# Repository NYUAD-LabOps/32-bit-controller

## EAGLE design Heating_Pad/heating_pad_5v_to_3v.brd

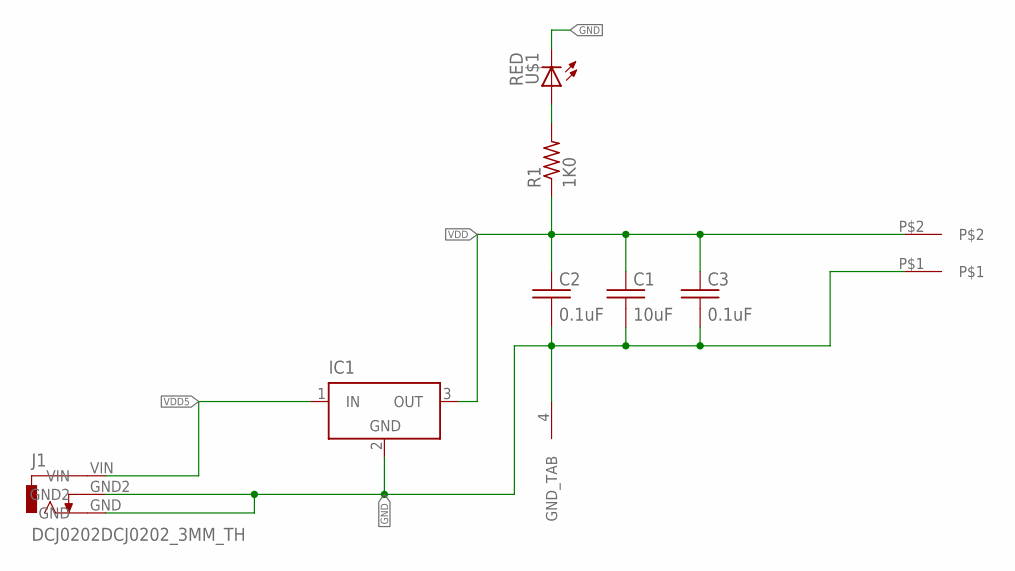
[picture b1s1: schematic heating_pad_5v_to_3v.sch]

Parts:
C1: 10uF; 0402
C2, C3: 0.1uF; 0402
IC1: LT1129CST3; SOT223
J1: DCJ0202DCJ0202_3MM_TH; DCJ0202_3MM_TH
J2: 2-pos; 2_3.81MM_PITCH
R1: 1K0; 0402
U$1: LED_0805_RED

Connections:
GND: C1.P$2 (2), C2.P$2 (2), C3.P$2 (2), IC1.2 (GND), IC1.4 (GND_TAB), J1.GND, J1.GND2, J2.P$1, U$1.C
unnamed: R1.P$2 (2), U$1.A
VDD: C1.P$1 (1), C2.P$1 (1), C3.P$1 (1), IC1.3 (OUT), J2.P$2, R1.P$1 (1)
VDD5: IC1.1 (IN), J1.VIN

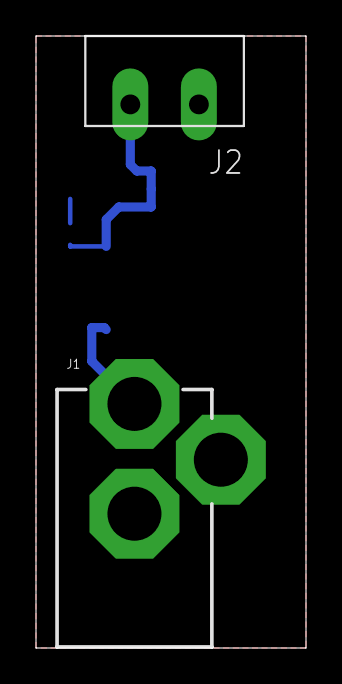
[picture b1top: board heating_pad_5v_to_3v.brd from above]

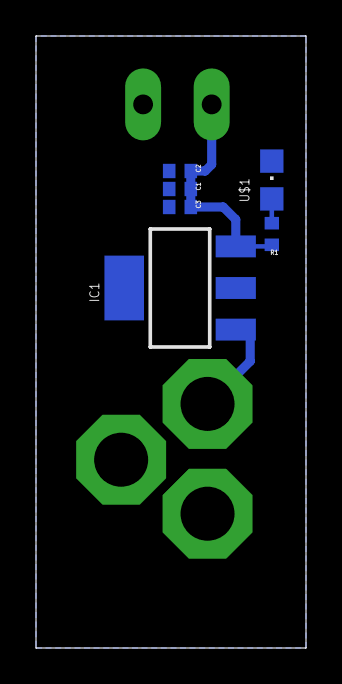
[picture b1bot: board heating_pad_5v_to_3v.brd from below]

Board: 2 copper layers, 15.0 x 34.0 mm, 8 parts (6 on the bottom side), 4 nets.

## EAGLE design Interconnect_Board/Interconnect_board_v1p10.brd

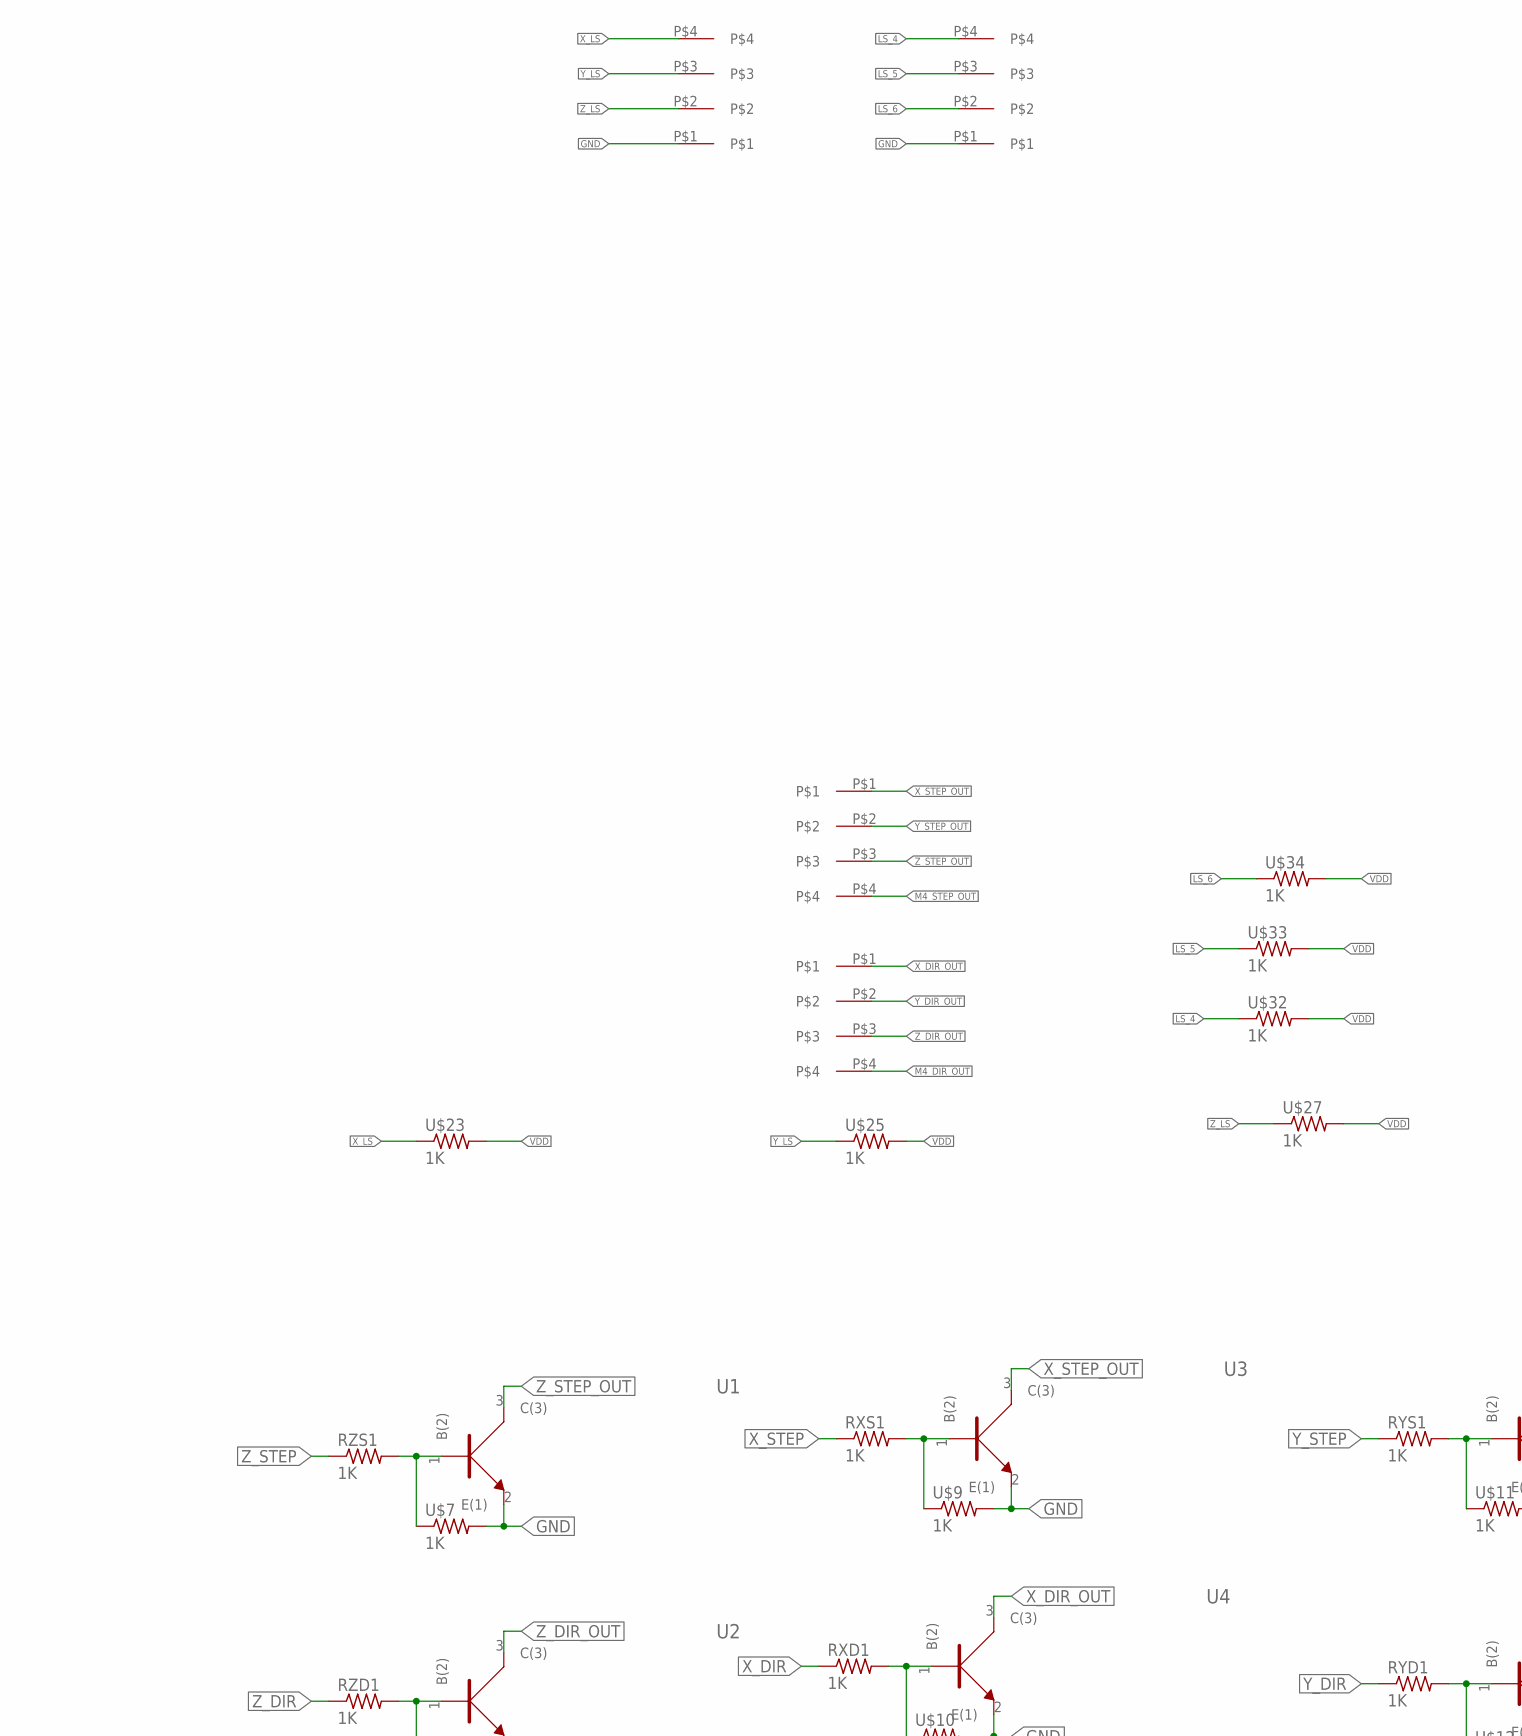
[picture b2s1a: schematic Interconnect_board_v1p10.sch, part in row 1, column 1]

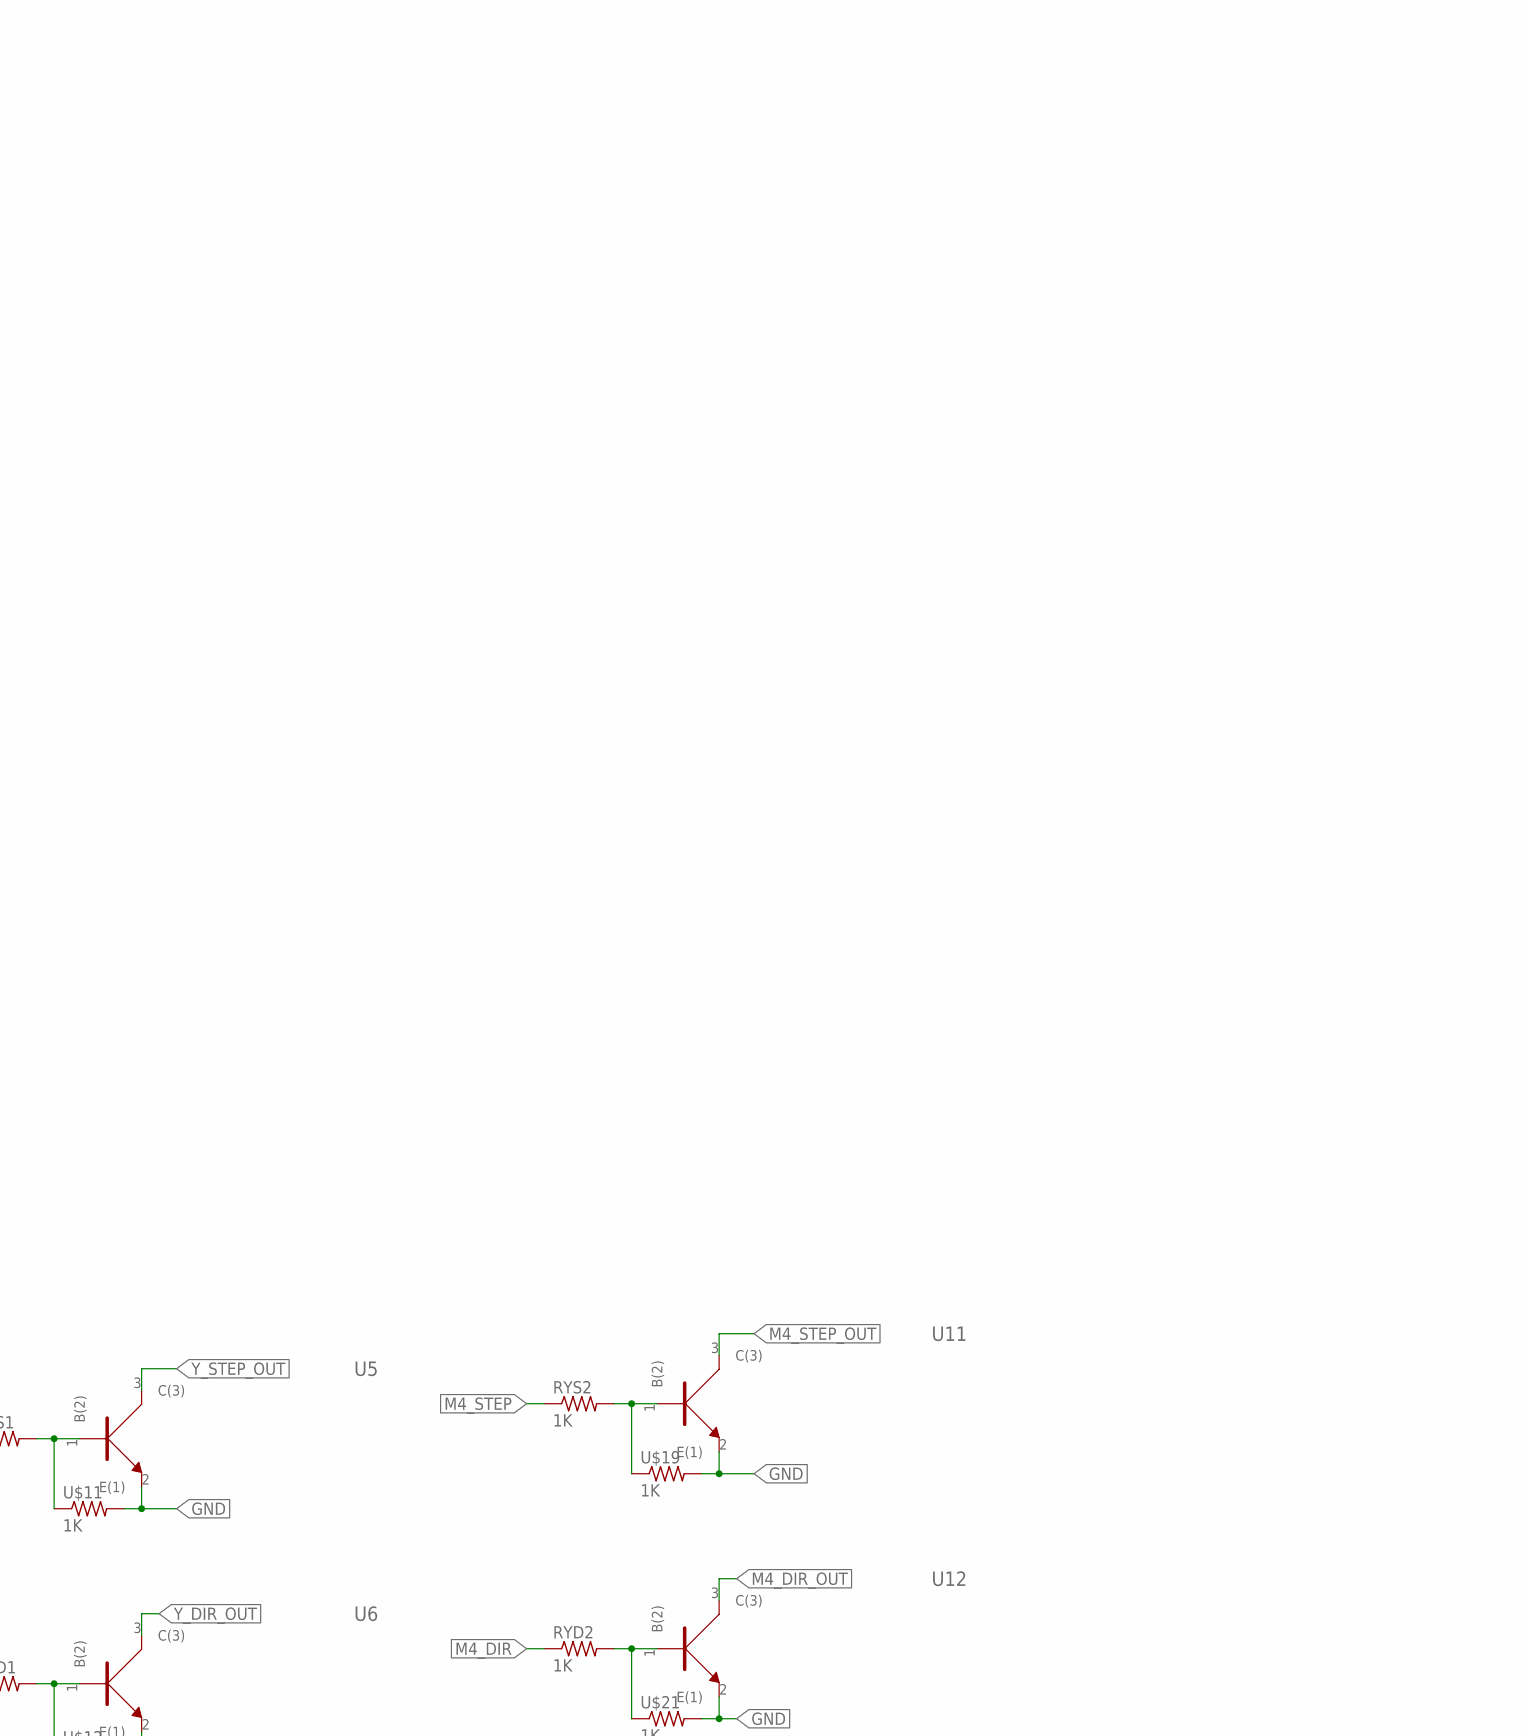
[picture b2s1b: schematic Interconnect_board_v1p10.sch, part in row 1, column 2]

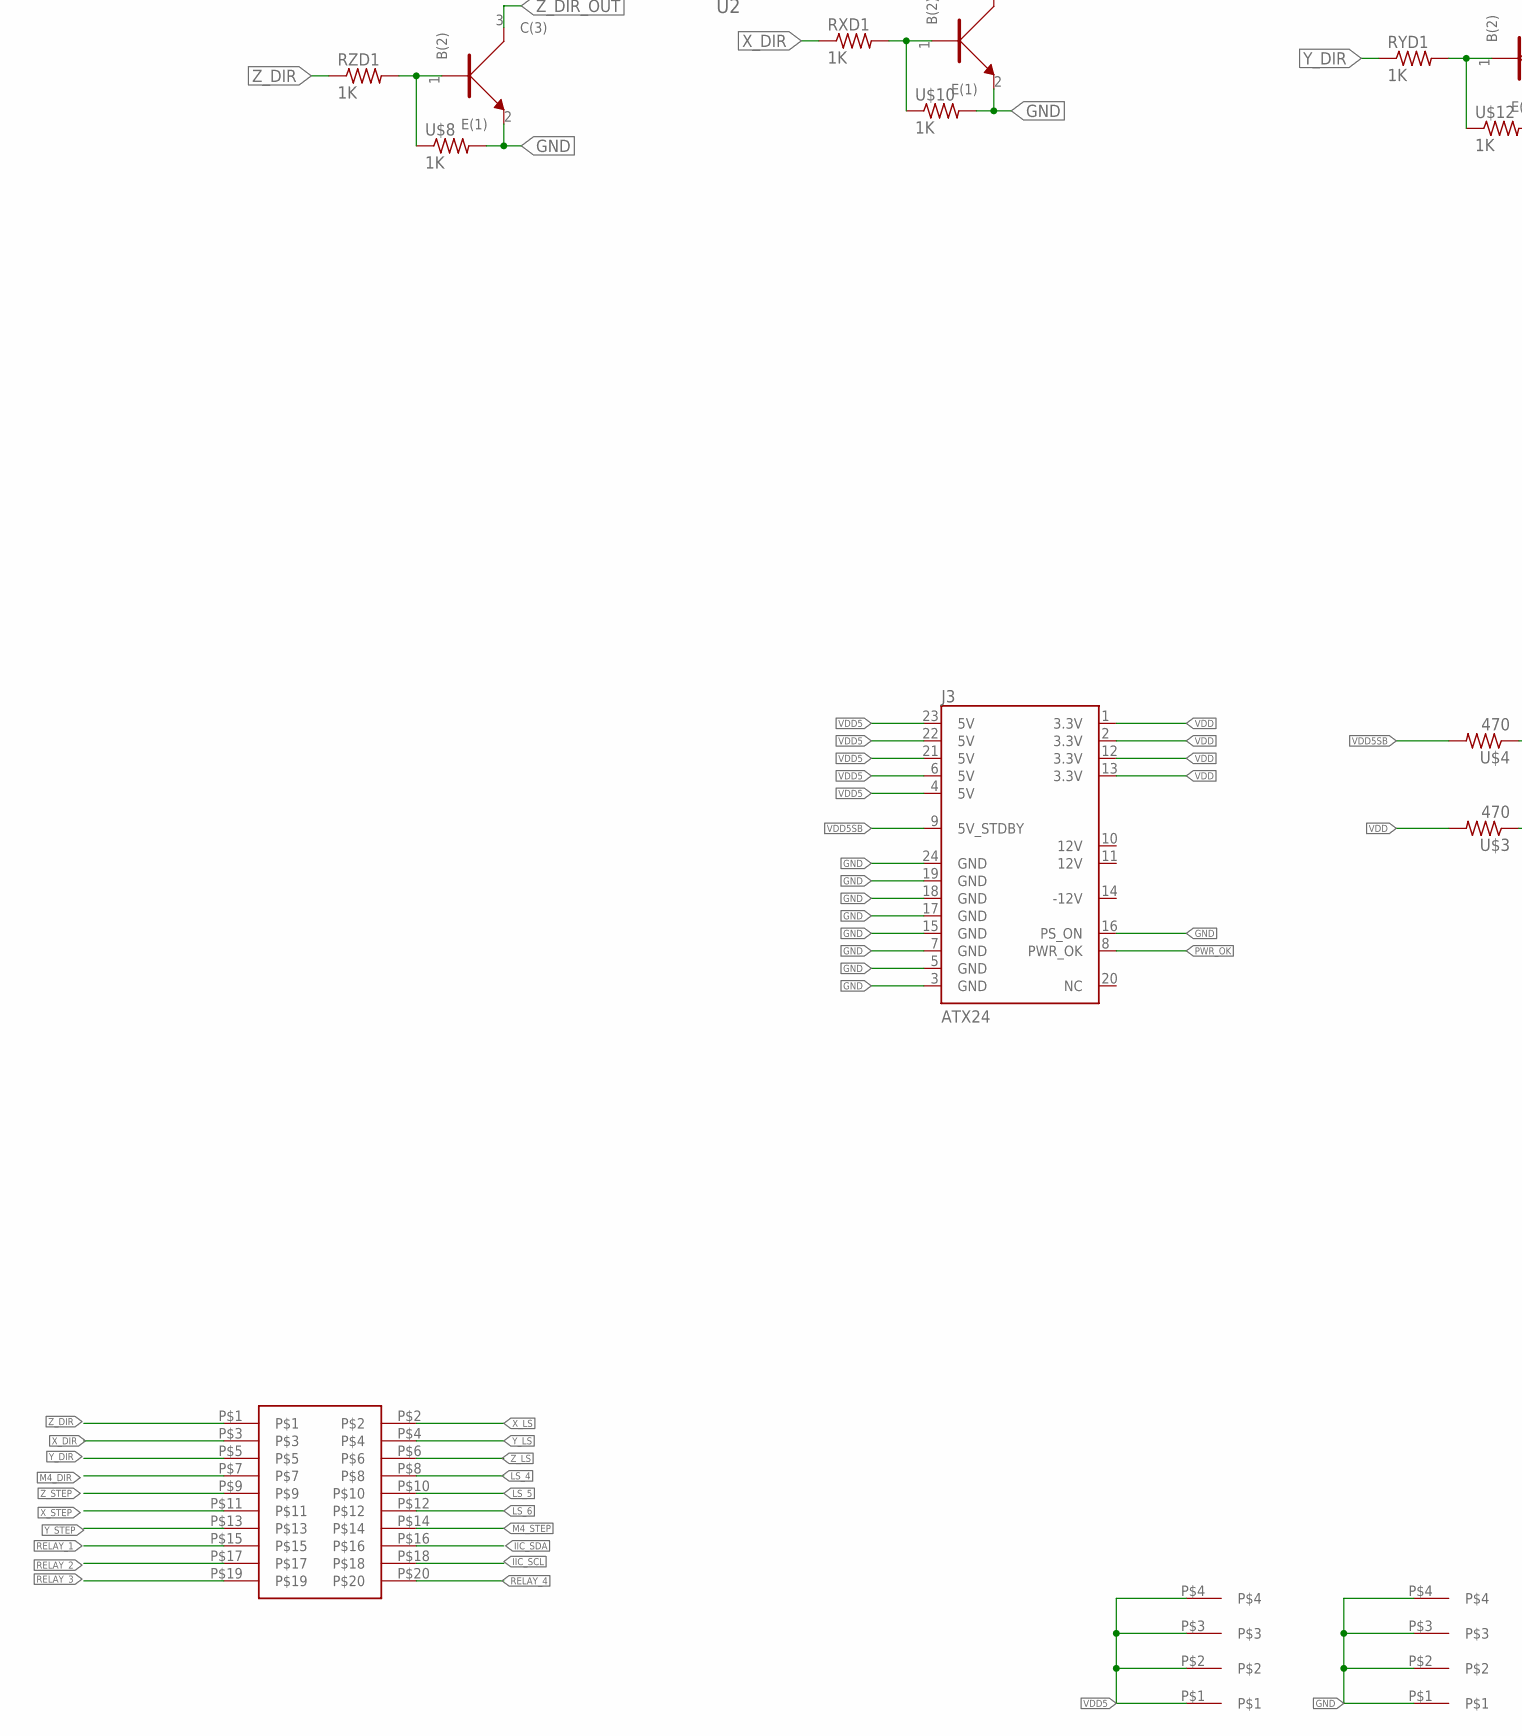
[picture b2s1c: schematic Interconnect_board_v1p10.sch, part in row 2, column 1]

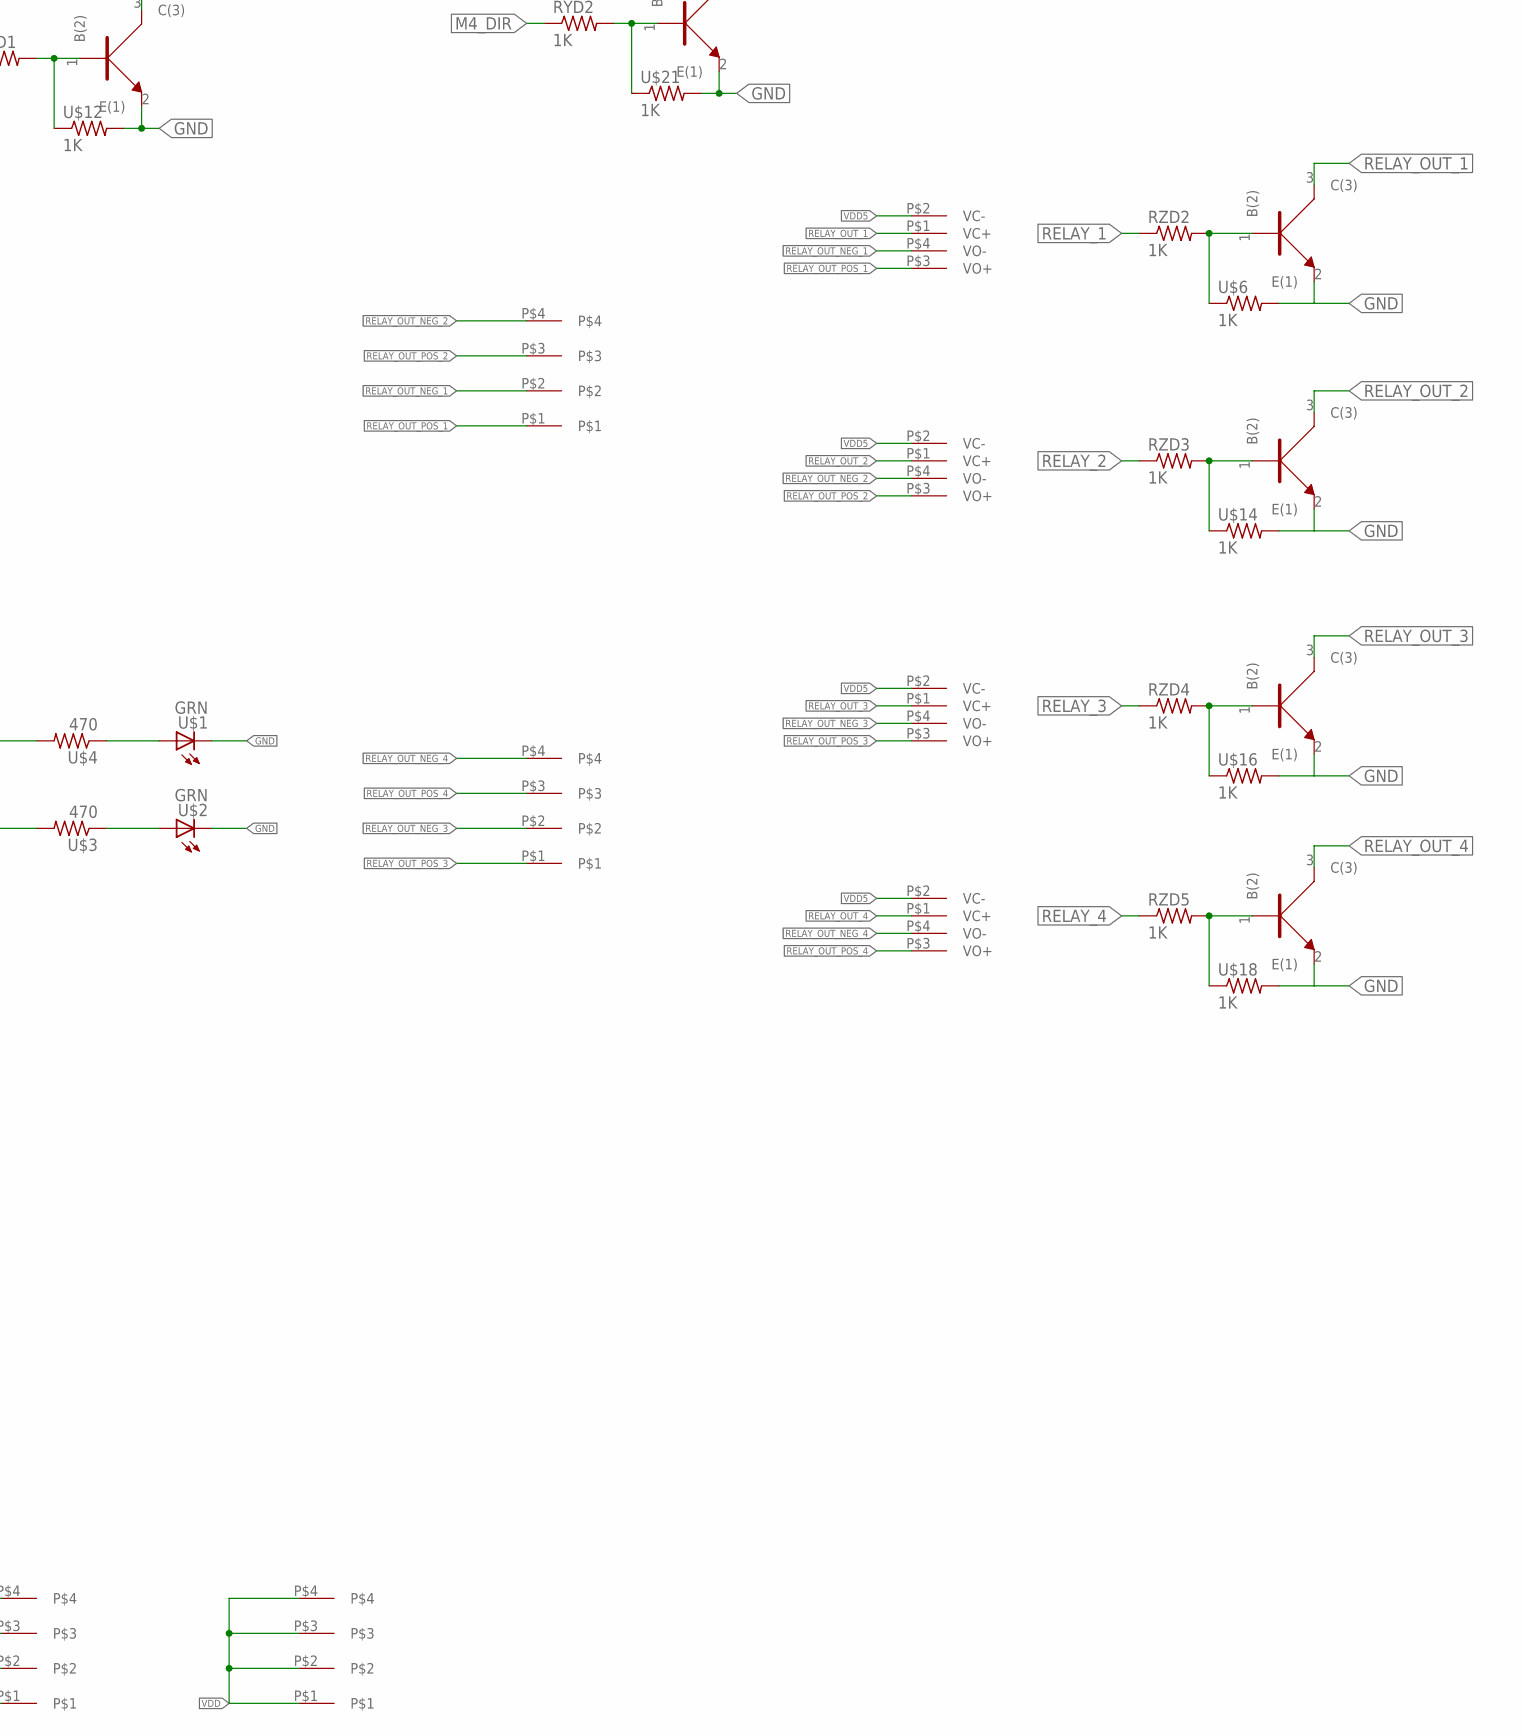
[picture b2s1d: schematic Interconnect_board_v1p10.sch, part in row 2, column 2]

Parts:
J1, J2, J4, J6, J7, J8, J9, J10, J11: 3.81MM_1_X_4_RT_ANGLE_PLUG_HEADER; 1X4_3.81MM_PITCH
J3: ATX24; ATX24_STRAIGHT
RXD1: R_0805_1K
RXS1: R_0805_1K
RYD1, RYD2: R_0805_1K
RYS1, RYS2: R_0805_1K
RZD1, RZD2, RZD3, RZD4, RZD5: R_0805_1K
RZS1: R_0805_1K
U1, U2, U3, U4, U5, U6, U7, U8, U9, U10, U11, U12: BC846BW; SOT323
U$1, U$2: LED_0805_GREEN
U$3, U$4: R_0805_470
U$5, U$13, U$15, U$17: RELAY_KYOTO_KF0604D
U$6, U$7, U$8, U$9, U$10, U$11, U$12, U$14, U$16, U$18, U$19, U$21, U$23, U$25, U$27, U$32, U$33, U$34: R_0805_1K
U$26: 2_X_10_HEADER_GENERIC; 2_X_10_.1_INCH

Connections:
GND: J1.P$1, J1.P$2, J1.P$3, J1.P$4, J3.3 (GND), J3.5 (GND), J3.7 (GND), J3.15 (GND), J3.16 (PS_ON), J3.17 (GND), J3.18 (GND), J3.19 (GND), J3.24 (GND), J10.P$1, J11.P$1, U1.2 (E(1)), U2.2 (E(1)), U3.2 (E(1)), U4.2 (E(1)), U5.2 (E(1)), U6.2 (E(1)), U7.2 (E(1)), U8.2 (E(1)), U9.2 (E(1)), U10.2 (E(1)), U11.2 (E(1)), U12.2 (E(1)), U$1.C, U$2.C, U$6.2, U$7.2, U$8.2, U$9.2, U$10.2, U$11.2, U$12.2, U$14.2, U$16.2, U$18.2, U$19.2, U$21.2
IIC_SCL: U$26.P$18
IIC_SDA: U$26.P$16
LS_4: J11.P$4, U$26.P$8, U$32.1
LS_5: J11.P$3, U$26.P$10, U$33.1
LS_6: J11.P$2, U$26.P$12, U$34.1
M4_DIR: RYD2.1, U$26.P$7
M4_DIR_OUT: J9.P$4, U12.3 (C(3))
M4_STEP: RYS2.1, U$26.P$14
M4_STEP_OUT: J8.P$4, U11.3 (C(3))
unnamed: RXS1.2, U3.1 (B(2)), U$9.1
unnamed: RZD3.2, U8.1 (B(2)), U$14.1
unnamed: RZD1.2, U2.1 (B(2)), U$8.1
unnamed: U$1.A, U$4.1
unnamed: U$2.A, U$3.1
unnamed: RZD4.2, U9.1 (B(2)), U$16.1
unnamed: RZS1.2, U1.1 (B(2)), U$7.1
unnamed: RZD2.2, U7.1 (B(2)), U$6.1
unnamed: RYS1.2, U5.1 (B(2)), U$11.1
unnamed: RZD5.2, U10.1 (B(2)), U$18.1
unnamed: RXD1.2, U4.1 (B(2)), U$10.1
unnamed: RYD1.2, U6.1 (B(2)), U$12.1
unnamed: RYS2.2, U11.1 (B(2)), U$19.1
unnamed: RYD2.2, U12.1 (B(2)), U$21.1
PWR_OK: J3.8 (PWR_OK)
RELAY_1: RZD2.1, U$26.P$15
RELAY_2: RZD3.1, U$26.P$17
RELAY_3: RZD4.1, U$26.P$19
RELAY_4: RZD5.1, U$26.P$20
RELAY_OUT_1: U7.3 (C(3)), U$5.P$1 (VC+)
RELAY_OUT_2: U8.3 (C(3)), U$13.P$1 (VC+)
RELAY_OUT_3: U9.3 (C(3)), U$15.P$1 (VC+)
RELAY_OUT_4: U10.3 (C(3)), U$17.P$1 (VC+)
RELAY_OUT_NEG_1: J6.P$2, U$5.P$4 (VO-)
RELAY_OUT_NEG_2: J6.P$4, U$13.P$4 (VO-)
RELAY_OUT_NEG_3: J7.P$2, U$15.P$4 (VO-)
RELAY_OUT_NEG_4: J7.P$4, U$17.P$4 (VO-)
RELAY_OUT_POS_1: J6.P$1, U$5.P$3 (VO+)
RELAY_OUT_POS_2: J6.P$3, U$13.P$3 (VO+)
RELAY_OUT_POS_3: J7.P$1, U$15.P$3 (VO+)
RELAY_OUT_POS_4: J7.P$3, U$17.P$3 (VO+)
VDD: J2.P$1, J2.P$2, J2.P$3, J2.P$4, J3.1 (3.3V), J3.2 (3.3V), J3.12 (3.3V), J3.13 (3.3V), U$3.2, U$23.2, U$25.2, U$27.2, U$32.2, U$33.2, U$34.2
VDD5: J3.4 (5V), J3.6 (5V), J3.21 (5V), J3.22 (5V), J3.23 (5V), J4.P$1, J4.P$2, J4.P$3, J4.P$4, U$5.P$2 (VC-), U$13.P$2 (VC-), U$15.P$2 (VC-), U$17.P$2 (VC-)
VDD5SB: J3.9 (5V_STDBY), U$4.2
X_DIR: RXD1.1, U$26.P$3
X_DIR_OUT: J9.P$1, U4.3 (C(3))
X_LS: J10.P$4, U$23.1, U$26.P$2
X_STEP: RXS1.1, U$26.P$11
X_STEP_OUT: J8.P$1, U3.3 (C(3))
Y_DIR: RYD1.1, U$26.P$5
Y_DIR_OUT: J9.P$2, U6.3 (C(3))
Y_LS: J10.P$3, U$25.1, U$26.P$4
Y_STEP: RYS1.1, U$26.P$13
Y_STEP_OUT: J8.P$2, U5.3 (C(3))
Z_DIR: RZD1.1, U$26.P$1
Z_DIR_OUT: J9.P$3, U2.3 (C(3))
Z_LS: J10.P$2, U$26.P$6, U$27.1
Z_STEP: RZS1.1, U$26.P$9
Z_STEP_OUT: J8.P$3, U1.3 (C(3))

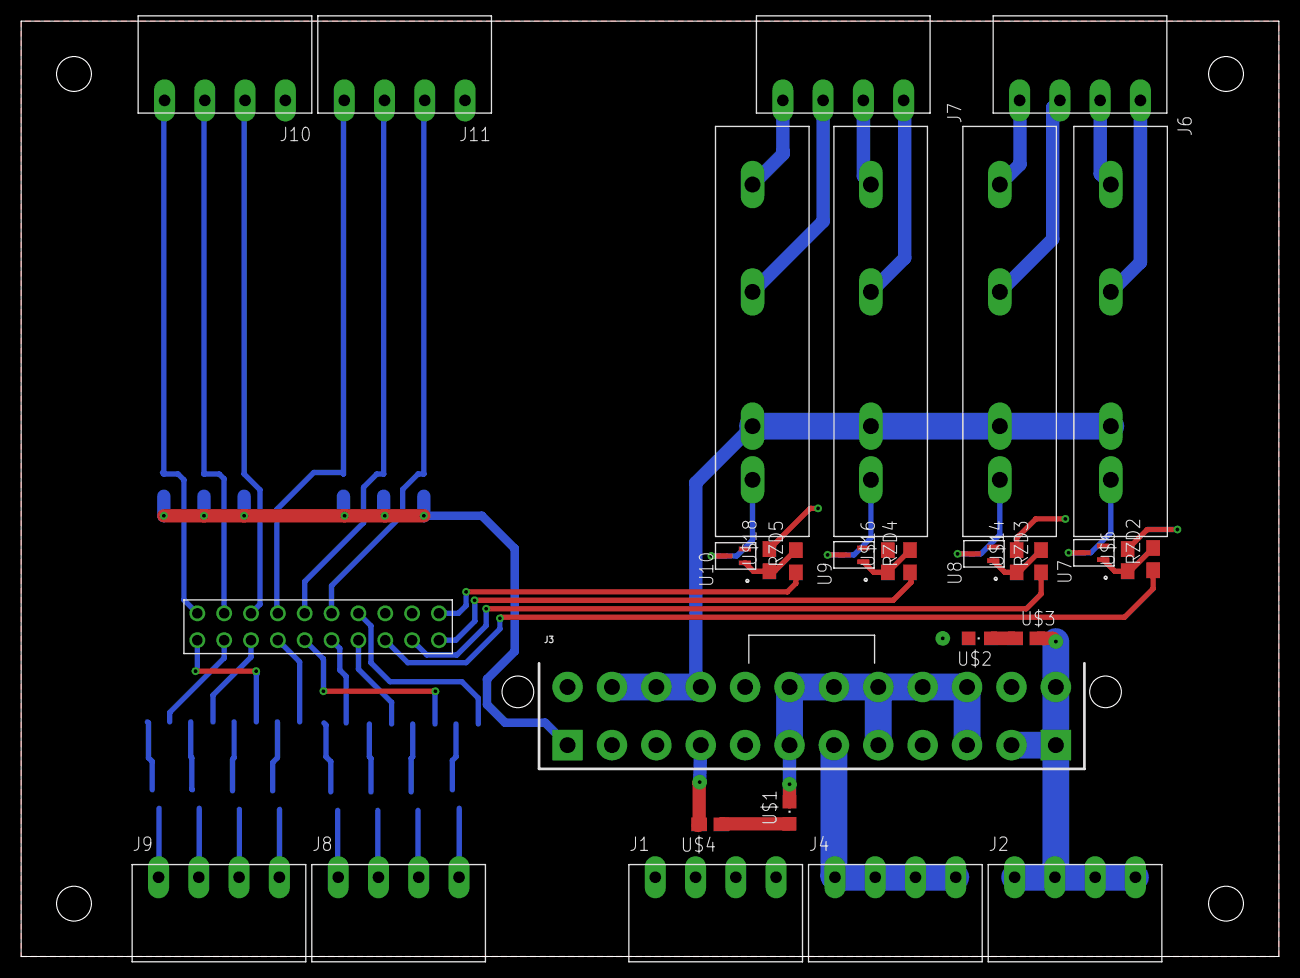
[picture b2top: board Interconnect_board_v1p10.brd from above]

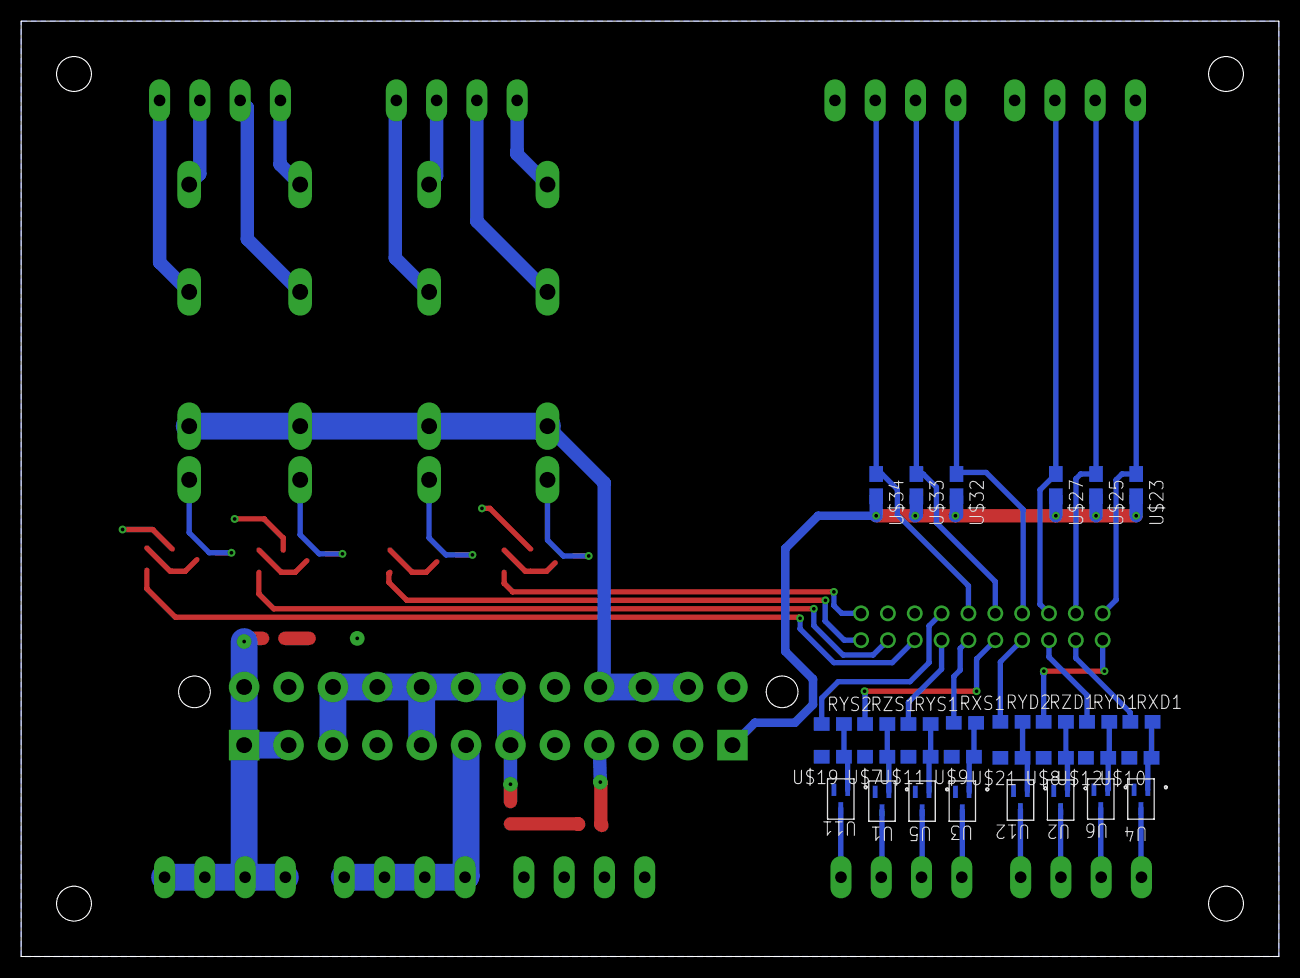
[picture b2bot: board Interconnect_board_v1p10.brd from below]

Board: 2 copper layers, 119.0 x 88.5 mm, 61 parts (30 on the bottom side), 56 nets.

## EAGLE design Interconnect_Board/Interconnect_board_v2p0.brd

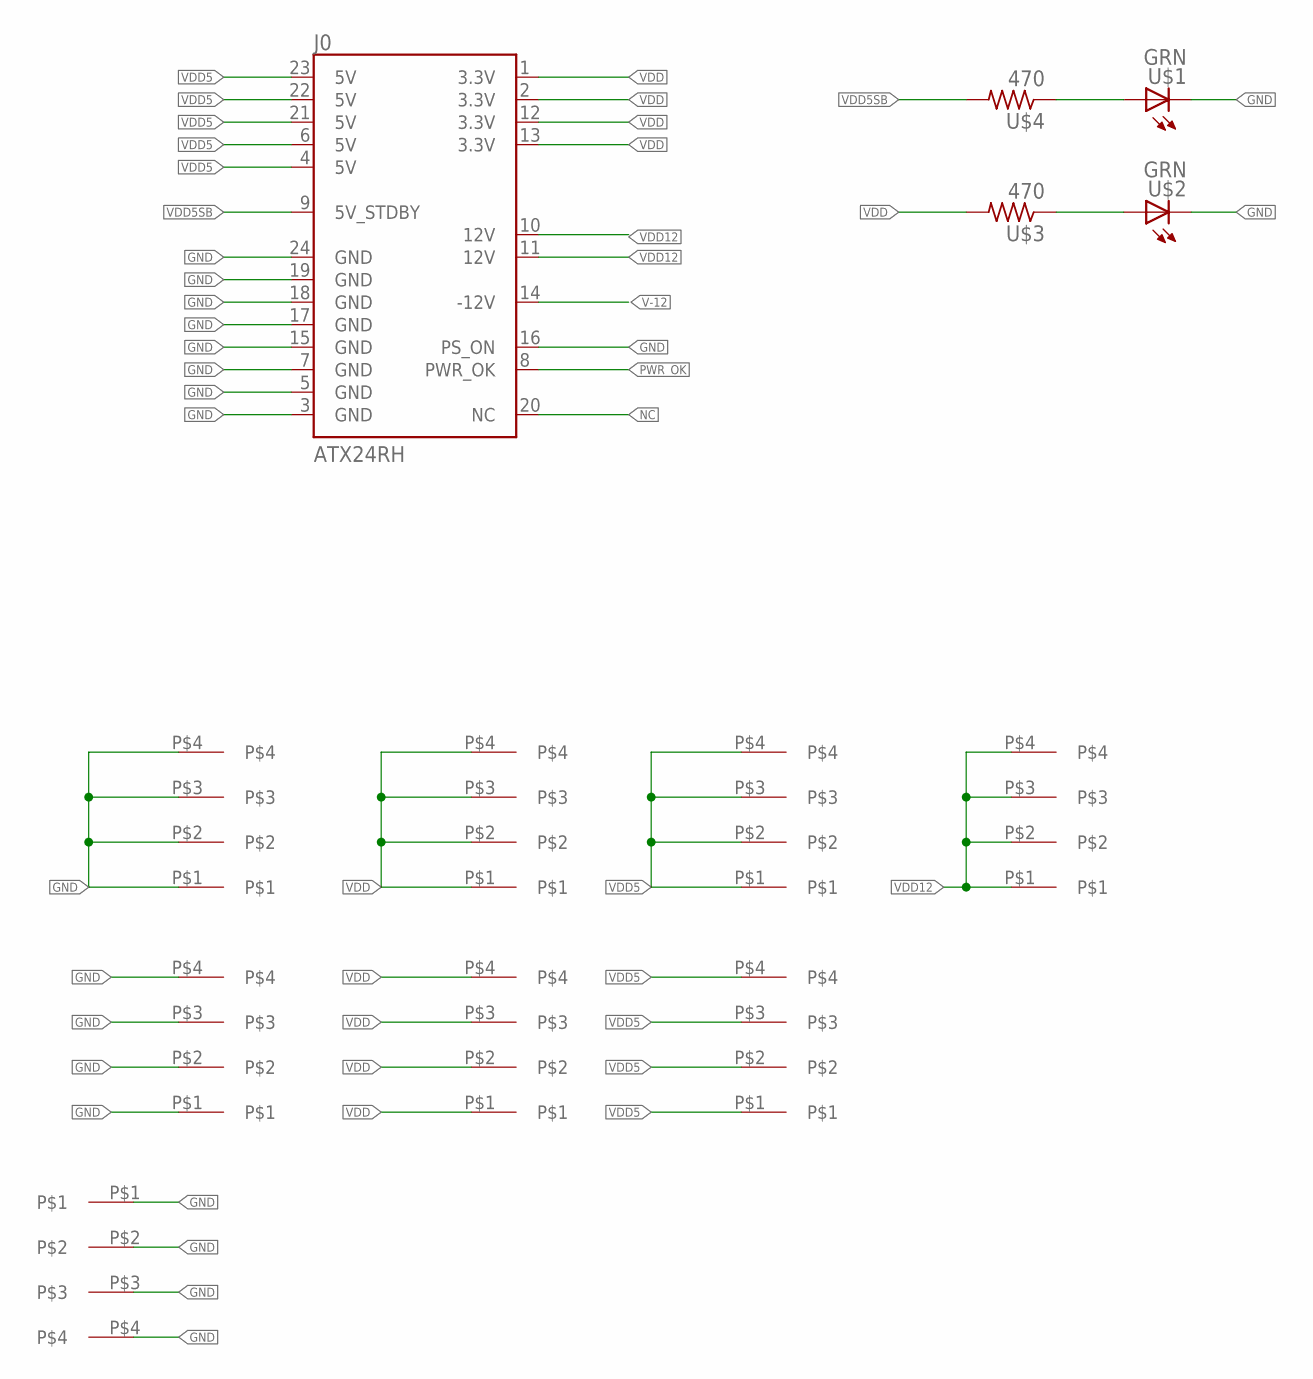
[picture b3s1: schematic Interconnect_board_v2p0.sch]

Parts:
J0: ATX24RH; ATX24_RIGHT_ANGLE
J1, J2, J3, J11, J12, J21, J22, J41: 3.81MM_1_X_4_RT_ANGLE_PLUG_HEADER; 1X4_3.81MM_PITCH
U$1, U$2: LED_0805_GREEN
U$3, U$4: R_0805_470

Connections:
GND: J0.3 (GND), J0.5 (GND), J0.7 (GND), J0.15 (GND), J0.16 (PS_ON), J0.17 (GND), J0.18 (GND), J0.19 (GND), J0.24 (GND), J1.P$1, J1.P$2, J1.P$3, J1.P$4, J2.P$1, J2.P$2, J2.P$3, J2.P$4, J3.P$1, J3.P$2, J3.P$3, J3.P$4, U$1.C, U$2.C
unnamed: U$1.A, U$4.1
unnamed: U$2.A, U$3.1
NC: J0.20 (NC)
PWR_OK: J0.8 (PWR_OK)
V-12: J0.14 (-12V)
VDD: J0.1 (3.3V), J0.2 (3.3V), J0.12 (3.3V), J0.13 (3.3V), J11.P$1, J11.P$2, J11.P$3, J11.P$4, J12.P$1, J12.P$2, J12.P$3, J12.P$4, U$3.2
VDD5: J0.4 (5V), J0.6 (5V), J0.21 (5V), J0.22 (5V), J0.23 (5V), J21.P$1, J21.P$2, J21.P$3, J21.P$4, J22.P$1, J22.P$2, J22.P$3, J22.P$4
VDD5SB: J0.9 (5V_STDBY), U$4.2
VDD12: J0.10 (12V), J0.11 (12V), J41.P$1, J41.P$2, J41.P$3, J41.P$4

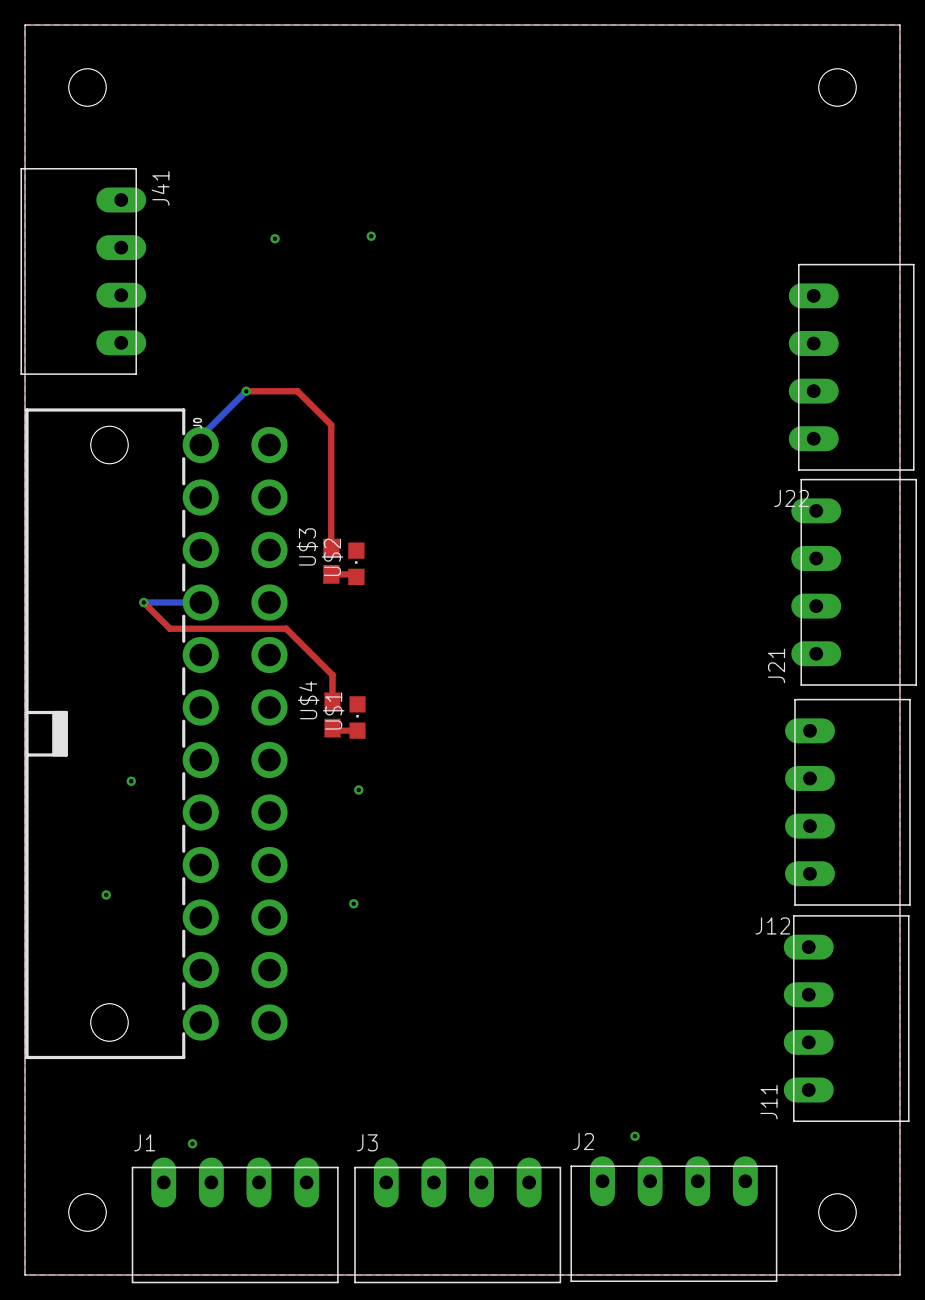
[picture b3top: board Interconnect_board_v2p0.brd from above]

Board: 2 copper layers, 70.0 x 100.0 mm, 13 parts (0 on the bottom side), 7 nets.

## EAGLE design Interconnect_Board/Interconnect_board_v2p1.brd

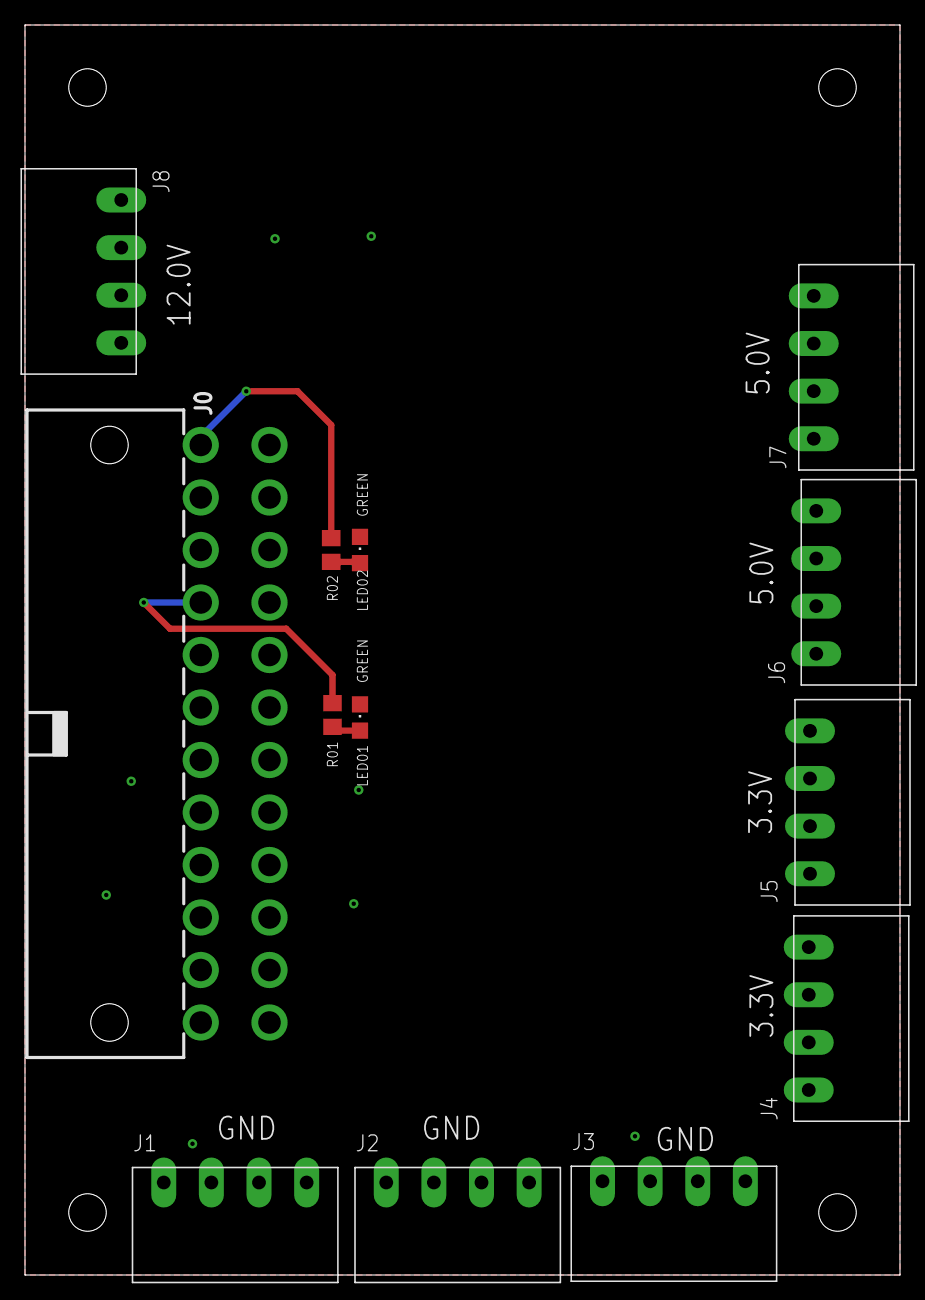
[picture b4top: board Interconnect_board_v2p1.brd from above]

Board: 2 copper layers, 70.0 x 100.0 mm, 13 parts (0 on the bottom side), 7 nets.

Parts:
J0: ATX24RH; ATX24_RIGHT_ANGLE
J1, J2, J3, J4, J5, J6, J7, J8: 1X4_3.81MM_PITCH
LED01, LED02: GREEN; LED_0805_GREEN
R01, R02: 470; 0805

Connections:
J2: J0.3, J0.5, J0.7, J0.15, J0.16, J0.17, J0.18, J0.19, J0.24, J1.P$1, J1.P$2, J1.P$3, J1.P$4, J2.P$1, J2.P$2, J2.P$3, J2.P$4, J3.P$1, J3.P$2, J3.P$3, J3.P$4, LED01.C, LED02.C
unnamed: LED01.A, R01.1
unnamed: LED02.A, R02.1
VDD: J0.1, J0.2, J0.12, J0.13, J4.P$1, J4.P$2, J4.P$3, J4.P$4, J5.P$1, J5.P$2, J5.P$3, J5.P$4, R02.2
VDD5: J0.4, J0.6, J0.21, J0.22, J0.23, J6.P$1, J6.P$2, J6.P$3, J6.P$4, J7.P$1, J7.P$2, J7.P$3, J7.P$4
VDD5SB: J0.9, R01.2
VDD12: J0.10, J0.11, J8.P$1, J8.P$2, J8.P$3, J8.P$4

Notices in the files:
parts and their libraries:
COPYRIGHT: Copyright (C) 2018 Accelerated Designs. All rights reserved
